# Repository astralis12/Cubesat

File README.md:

# UGMSat-2
A bachelor thesis final project aimed to create CubeSat for students in Indonesia with the approach of model-based system engineering in the field of aerospace

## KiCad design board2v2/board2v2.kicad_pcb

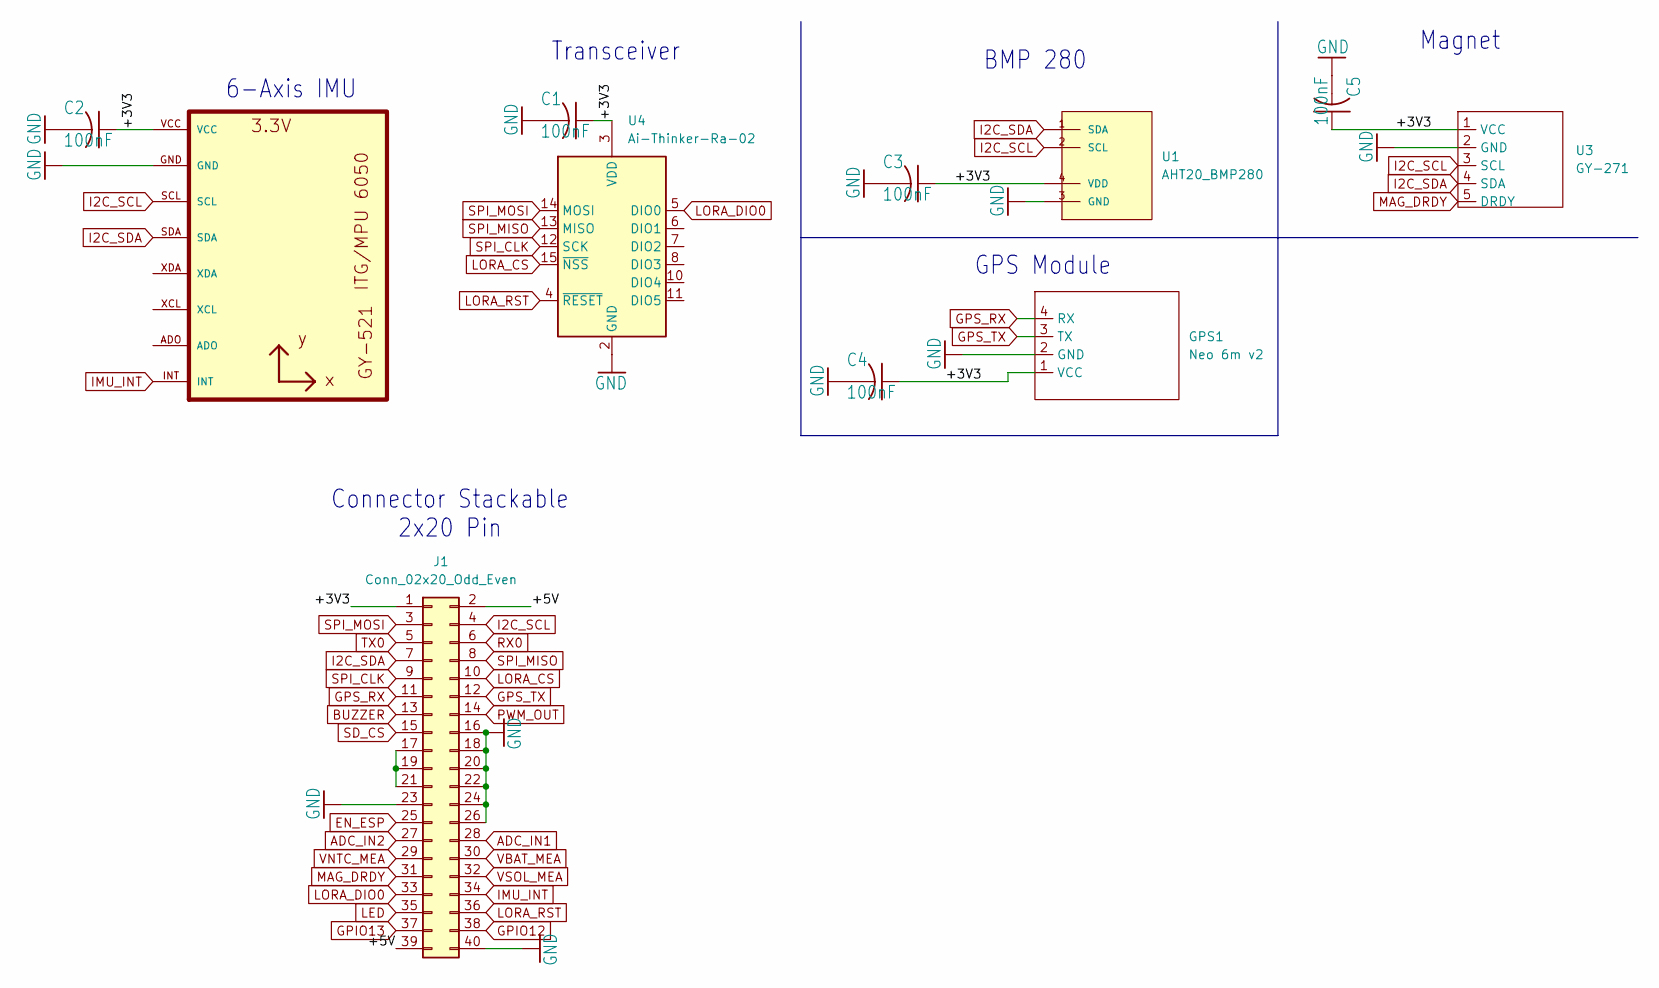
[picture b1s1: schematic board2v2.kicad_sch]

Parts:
C1, C2, C3, C4, C5: 100nF; C_0805_2012Metric_Pad1.18x1.45mm_HandSolder
GPS1: Neo 6m v2; NEO-6M-V2
J1: Conn_02x20_Odd_Even; PinSocket_2x20_P2.54mm_Vertical
U1: AHT20_BMP280
U2: GY-521
U3: GY-271
U4: Ai-Thinker-Ra-02; LORA SX1278 RA-02 WIRELESS MODULE

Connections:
/+3V3: C1.1, C2.1, C3.1, C4.1, C5.1, GPS1.1 (VCC), J1.1, U1.4 (VDD), U2.VCC, U3.1 (VCC), U4.3 (VDD)
/+5V: J1.2, J1.39
ADC_IN1: J1.28
ADC_IN2: J1.27
BUZZER: J1.13
EN_ESP: J1.25
GND: C1.2, C2.2, C3.2, C4.2, C5.2, GPS1.2 (GND), J1.16, J1.18, J1.20, J1.22, J1.23, J1.24, J1.26, J1.40, U1.3 (GND), U2.GND, U3.2 (GND), U4.1 (GND), U4.2 (GND), U4.9 (GND), U4.16 (GND)
GPIO12: J1.38
GPIO13: J1.37
GPS_RX: GPS1.4 (RX), J1.11
GPS_TX: GPS1.3 (TX), J1.12
I2C_SCL: J1.4, U1.2 (SCL), U2.SCL, U3.3 (SCL)
I2C_SDA: J1.7, U1.1 (SDA), U2.SDA, U3.4 (SDA)
IMU_INT: J1.34, U2.INT
LED: J1.35
LORA_CS: J1.10, U4.15 (~NSS)
LORA_DIO0: J1.33, U4.5 (DIO0)
LORA_RST: J1.36, U4.4 (~RESET)
MAG_DRDY: J1.31, U3.5 (DRDY)
unnamed: J1.17, J1.19, J1.21
PWM_OUT: J1.14
RX0: J1.6
SD_CS: J1.15
SPI_CLK: J1.9, U4.12 (SCK)
SPI_MISO: J1.8, U4.13 (MISO)
SPI_MOSI: J1.3, U4.14 (MOSI)
TX0: J1.5
VBAT_MEA: J1.30
VNTC_MEA: J1.29
VSOL_MEA: J1.32

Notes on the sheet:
Magnet
GPS Module
Transceiver
6-Axis IMU
BMP 280
Connector Stackable 2x20 Pin

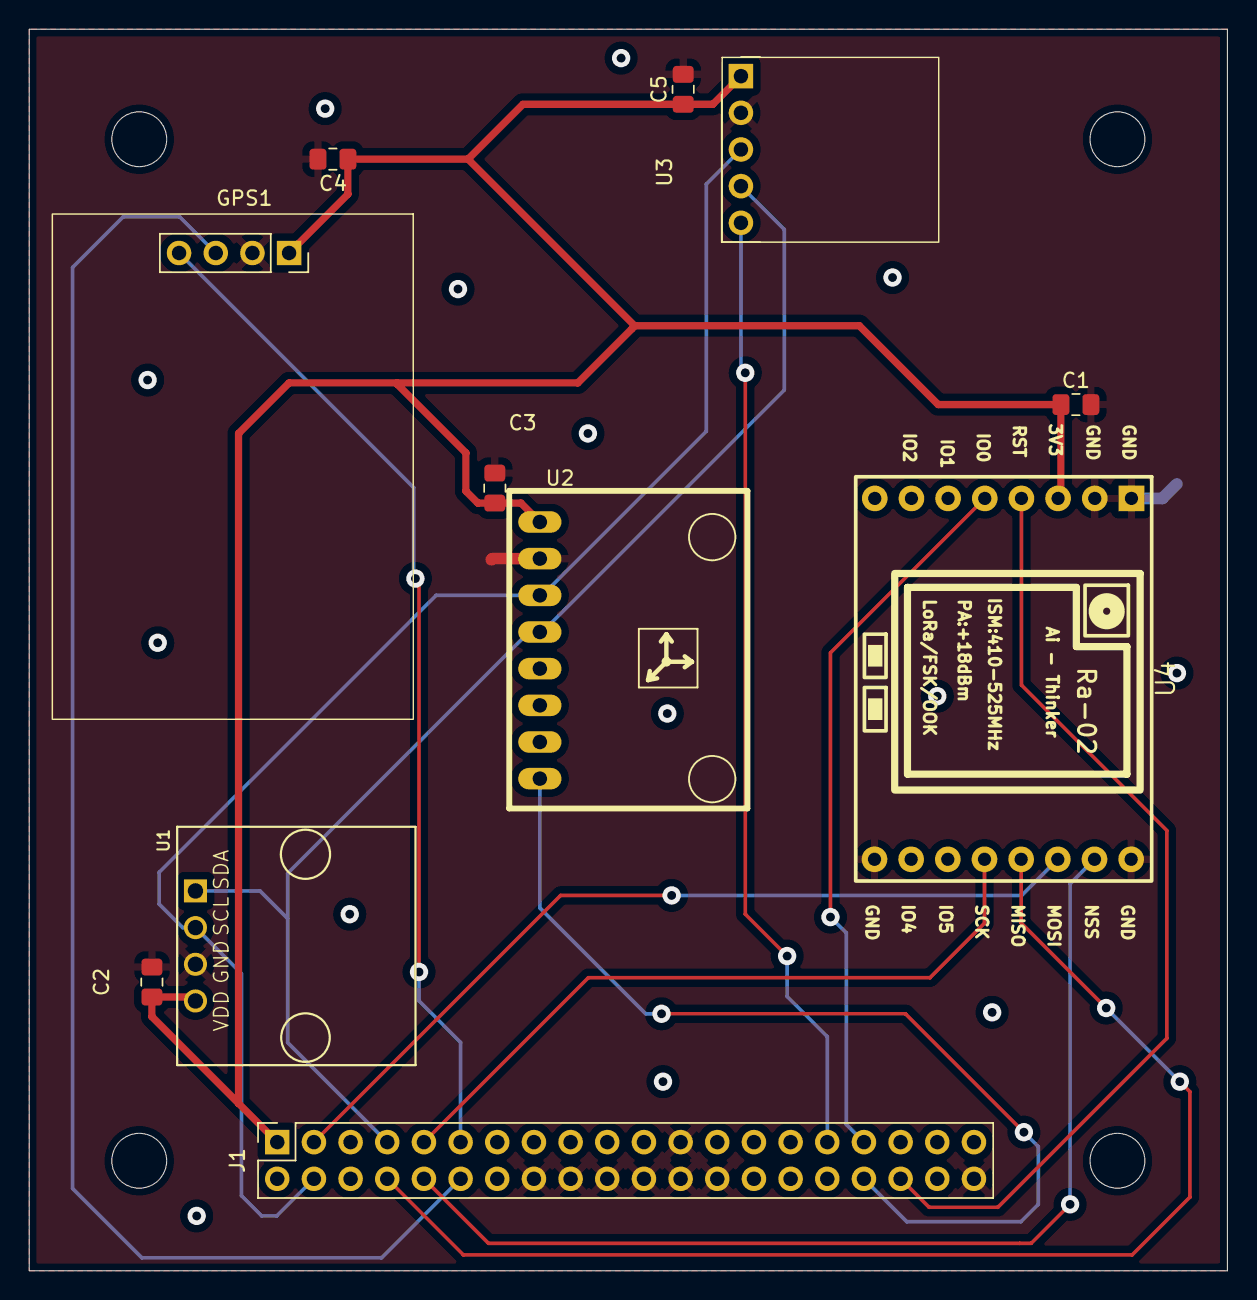
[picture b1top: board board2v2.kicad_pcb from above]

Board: 2 copper layers, 83.0 x 86.0 mm, 11 parts (0 on the bottom side), 16 nets.

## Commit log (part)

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2025-10-12 example for git
2025-10-12 second trial
2025-10-12 0 MBSE backbone v1
2025-11-29 Printed OBC and EPS
    double layer minus the interface documentation
